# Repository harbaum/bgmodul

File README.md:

# BG-Modul

Unterlagen zum Produkt-Modul am Bismarck-Gymnasium.

Dieses Repository enthält die Schaltpläne und Platinenunterlagen
als PDF und im Original-Eagle-Format. Die Dateien können mit der
Test-Version von Eagle geöffnet werden.

Das Demo-Program bgmeter.ino kann in der Arduino-IDE geöffnet
werden. Es benötigt als zusätzliche Bibliotheken

  - ```VL53L0X distance sensor library``` von Pololu für den Laser-Sensor
  - ```TFT_ST7735 library``` von Bodmer für das Display

In der Datei ```User_Setup.h``` der TFT_ST7735-Bibliothek müssen
folgenden Zeilen angepasst werden, damit korrekt eingestellt ist an
welchen Anschlüssen des Prozessors das Display angeschlossen ist:

```
// ###### EDIT THE PIN NUMBERS IN THE 3 LINES FOLLOWING TO SUIT YOUR SETUP ######

#define TFT_CS  10  // Chip select control pin
#define TFT_DC  8  // Data Command control pin
#define TFT_RST 9  // Reset pin (could connect to Arduino RESET pin)
```

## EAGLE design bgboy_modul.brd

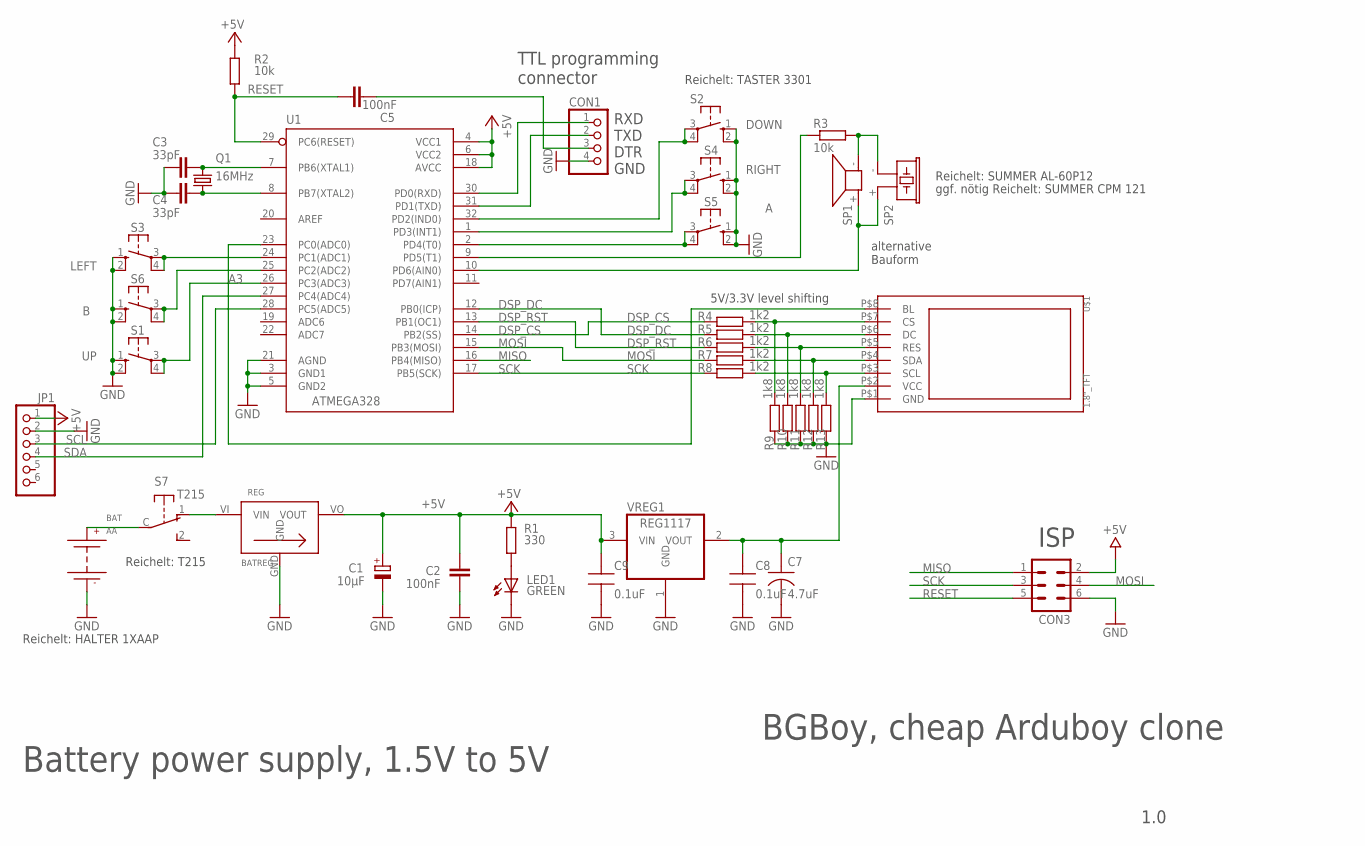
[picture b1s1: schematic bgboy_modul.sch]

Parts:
BAT: AA; 1XAAP
C1: 10µF; SMC_D
C2, C5: 100nF; C0805
C3, C4: 33pF; C0805
C7: 4.7uF; TAN-A
C8, C9: 0.1uF; CAP0805-NP
CON1: PINHD-1X4/90; 1X04/90
CON3: MA03-2
JP1: PINHD-1X6; 1X06
LED1: GREEN; LED3MM
Q1: 16MHz; HC49UP
R1: 330; R0805
R2, R3: 10k; R0805
R4, R5, R6, R7, R8: 1k2; M0805
R9, R10, R11, R12, R13: 1k8; M0805
REG: BATREG
S1: UP; B3F-10XX
S2: DOWN; B3F-10XX
S3: LEFT; B3F-10XX
S4: RIGHT; B3F-10XX
S5: A; B3F-10XX
S6: B; B3F-10XX
S7: T215
SP1: KSS1201
SP2: F/CM12P
U1: ATMEGA328; QFP032
U$1: 1.8"_TFT
VREG1: REG1117; SOT223

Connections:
+5V: C1.+, C2.2, C9.1, JP1.1, R1.1, R2.2, REG.VO (VOUT), U1.4 (VCC1), U1.6 (VCC2), U1.18 (AVCC), VREG1.3 (VIN)
A0: U1.23 (PC0(ADC0)), U$1.P$8 (BL)
A1: S3.3, S3.4 (P1), U1.24 (PC1(ADC1))
A2: S6.3, S6.4 (P1), U1.25 (PC2(ADC2))
A3: S1.3, S1.4 (P1), U1.26 (PC3(ADC3))
D0: CON1.1, U1.30 (PD0(RXD))
D1: CON1.2, U1.31 (PD1(TXD))
D2: S2.3, S2.4 (P1), U1.32 (PD2(IND0))
D3: S4.3, S4.4 (P1), U1.1 (PD3(INT1))
D4: S5.3, S5.4 (P1), U1.2 (PD4(T0))
D5: R3.1, U1.9 (PD5(T1))
D7: SP1.+ (1), SP2.+ (1), U1.10 (PD6(AIN0))
DSP_CS: R4.1, U1.14 (PB2(SS))
DSP_DC: R5.1, U1.12 (PB0(ICP))
DSP_RST: R6.1, U1.13 (PB1(OC1))
GND: BAT.-, C1.-, C2.1, C3.1, C4.1, C7.2, C8.2, C9.2, CON1.4, CON3.6, JP1.2, LED1.K (C), R9.1, R10.1, R11.1, R12.1, R13.1, REG.GND, S1.1 (S), S1.2 (S1), S2.1 (S), S2.2 (S1), S3.1 (S), S3.2 (S1), S4.1 (S), S4.2 (S1), S5.1 (S), S5.2 (S1), S6.1 (S), S6.2 (S1), U1.3 (GND1), U1.5 (GND2), U1.21 (AGND), U$1.P$1 (GND), VREG1.1 (GND)
MISO: CON3.1, U1.16 (PB4(MISO))
MOSI: CON3.4, R7.1, U1.15 (PB3(MOSI))
unnamed: C4.2, Q1.1, U1.8 (PB7(XTAL2))
unnamed: C3.2, Q1.2, U1.7 (PB6(XTAL1))
unnamed: LED1.A, R1.2
unnamed: REG.VI (VIN), S7.1 (O)
unnamed: BAT.+, S7.C
unnamed: R4.2, R9.2, U$1.P$7 (CS)
unnamed: R6.2, R11.2, U$1.P$5 (RES)
unnamed: R3.2, SP1.- (2), SP2.- (2)
unnamed: R5.2, R10.2, U$1.P$6 (DC)
unnamed: C5.2, CON1.3
unnamed: C7.1, C8.1, U$1.P$2 (VCC), VREG1.2 (VOUT)
unnamed: R7.2, R12.2, U$1.P$4 (SDA)
unnamed: R8.2, R13.2, U$1.P$3 (SCL)
RESET: C5.1, CON3.5, R2.1, U1.29 (PC6(RESET))
SCK: CON3.3, R8.1, U1.17 (PB5(SCK))
SCL: JP1.3, U1.28 (PC5(ADC5))
SDA: JP1.4, U1.27 (PC4(ADC4))
VCC: CON3.2

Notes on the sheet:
Reichelt: T215
Reichelt: HALTER 1XAAP
ggf. nötig Reichelt: SUMMER CPM 121
Reichelt: SUMMER AL-60P12
Reichelt: TASTER 3301
Battery power supply, 1.5V to 5V
TTL programming connector
BGBoy, cheap Arduboy clone
1.0
RXD TXD DTR GND
alternative Bauform
5V/3.3V level shifting
ISP

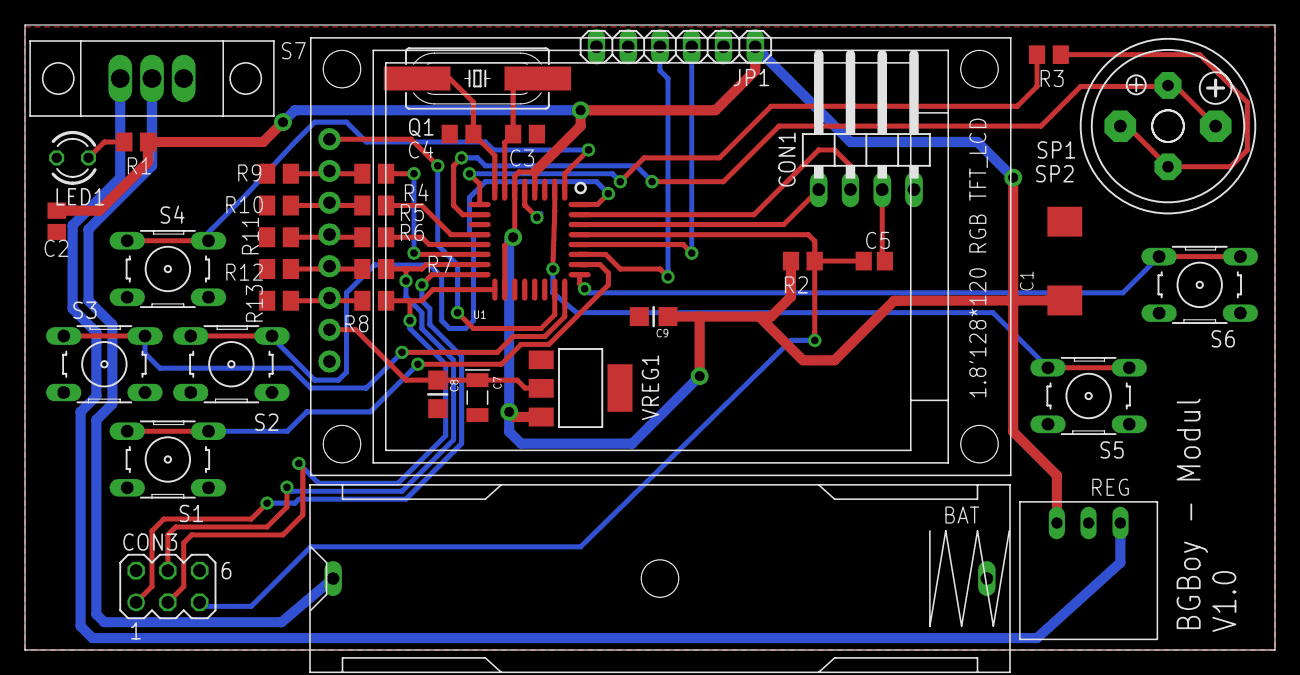
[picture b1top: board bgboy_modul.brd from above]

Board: 2 copper layers, 100.0 x 50.0 mm, 40 parts (0 on the bottom side), 35 nets.
